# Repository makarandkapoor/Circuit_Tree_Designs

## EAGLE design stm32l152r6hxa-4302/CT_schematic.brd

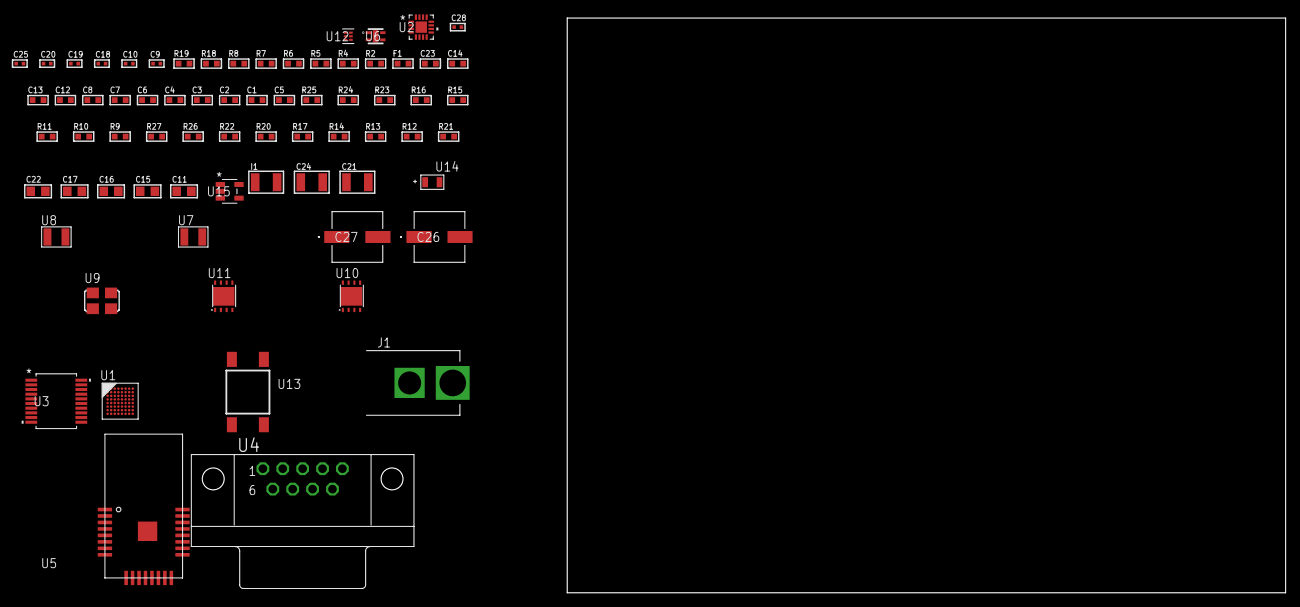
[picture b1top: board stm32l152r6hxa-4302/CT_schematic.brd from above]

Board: 2 copper layers, 100.0 x 80.0 mm, 71 parts (0 on the bottom side), 51 nets, no tracks yet.

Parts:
C1, C2, C3, C4, C6: 1e-07; C0603
C5: 4.7e-06; C0603
C7: 1e-08; C0603
C8, C12, C13, C14: 1e-06; C0603
C9, C10: 1e-11; C0402
C11, C15: 4.7e-06; C0805
C16, C17, C22: 1e-05; C0805
C18, C25: 1e-07; C0402
C19, C20, C28: 1e-08; C0402
C21, C24: 1e-05; C1210
C23: 8e-07; R0603
C26, C27: 0.0001; EXV-9H
F1: 240.0; L0603
I1: 1.5e-05; L1210
J1: PJ-037B; PJ-037B_PACKAGE
R2, R19: 1000.0; R0603
R4: 4700.0; R0603
R5, R6, R7, R8: 2200.0; R0603
R9, R10, R11, R15, R16, R23, R24: 10000.0; R0603
R12, R13, R14, R17, R20, R22: 100000.0; R0603
R18: 806.0; R0603
R21: 153694.38; R0603
R25: 82000.0; R0603
R26: 300000.0; R0603
R27: 120000.0; R0603
U1: STM32L152R6H6A; TFBGA64
U2: M41T65Q6F; M41T65_QFN-16
U3: MAX3218EAP+T; SSOP-20
U4: 182-009-113R531; 182-009-MALE
U5: ATBTLC1000-MR110CA
U6: Si7034-A10-IM; SI7034-A10-IM
U7, U8: ABS07-32.768KHZ-7-T
U9: ASFL1-25MHZ-NCS; ASFL1
U10: LP3878SDX-ADJ/NOPB; WSON-8
U11: LP2951ACSDX/NOPB; WSON-8
U12: TPS3895ADRYR; SON-6
U13: 4-1437565-2; SW_4-1437565-2
U14: Q65110A2395; LGM67K-G1J2-24-Z
U15: nc7sz125m5x; NC7SZ125M5X

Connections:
CLK_CRYSTAL_U1_A1: C9.1, U1.A1, U8.1
CLK_CRYSTAL_U1_B1: C10.1, U1.B1, U8.2
CLK_CRYSTAL_U2_1: U2.1, U7.1
CLK_CRYSTAL_U2_2: U2.2, U7.2
CLK_U1_C1: U1.C1, U9.3
GND: C1.2, C2.2, C3.2, C4.2, C5.2, C6.2, C7.2, C8.2, C9.2, C10.2, C11.2, C12.2, C13.2, C14.2, C16.2, C17.2, C18.2, C19.2, C20.2, C21.2, C22.2, C23.2, C24.2, C25.2, C26.2, C27.2, C28.2, J1.2, R2.2, R9.2, R19.2, R22.2, R25.2, R27.2, U1.C2, U1.D4, U1.D5, U1.D6, U1.F1, U2.3, U2.5, U2.17, U3.5, U3.17, U3.20, U4.5, U5.1, U5.9, U5.13, U5.24, U5.25, U6.5, U9.2, U10.3, U10.PAD, U11.3, U11.4, U11.PAD, U12.2, U14.C, U15.1, U15.3
NET_U1_A3: R6.1, U1.A3, U6.4
NET_U1_B2: C6.1, U1.B2
NET_U1_B3: R5.1, U1.B3, U6.2
NET_U1_B4: R9.1, U1.B4
NET_U1_E1: R4.1, U1.E1, U15.4
NET_U1_G7: R7.1, U1.G7, U2.10
NET_U1_H1: C7.1, C8.1, F1.1, U1.G1, U1.H1
NET_U1_H7: R8.1, U1.H7, U2.9
NET_U1_H8: U13.3, U13.4
NET_U2_4: R10.1, U2.4
NET_U2_11: R11.1, U2.11
NET_U3_1: I1.1, U3.1
NET_U3_2: R12.1, U3.2
NET_U3_3: R13.1, U3.3
NET_U3_4: R14.1, U3.4
NET_U3_15: C14.1, U3.15
NET_U3_16: C15.2, U3.16
NET_U3_18: C15.1, U3.18
NET_U3_19: C13.1, U3.19
NET_U4_2: U3.12, U4.2
NET_U4_3: U3.14, U4.3
NET_U4_7: U3.11, U4.7
NET_U4_8: U3.13, U4.8
NET_U5_17: R15.1, U5.17
NET_U5_20: R16.1, U5.20
NET_U10_1: C20.1, U10.1
NET_U10_6: R18.2, R19.1, U10.6
NET_U10_8: R17.1, U10.8
NET_U11_5: R20.1, U11.5
NET_U11_7: R21.2, R22.1, U11.7
NET_U12_1: R24.1, R25.1, U12.1
NET_U12_3: R26.2, R27.1, U12.3
NET_U12_4: R23.1, U12.4, U15.2
NET_U13_1: R2.1, U13.1, U13.2
PROC_SPI1_MISO: U1.A4, U5.14
PROC_SPI1_MOSI: U1.C4, U5.11
PROC_SPI1_NSS: U1.A6, U5.12
PROC_SPI1_SCK: U1.A5, U5.10
PROC_USART1_CTS: U1.C8, U3.8
PROC_USART1_RTS: U1.B8, U3.10
PROC_USART1_RX: U1.C3, U3.9
PROC_USART1_TX: U1.C7, U3.7
VCC_S1_15V4: C21.1, C23.1, C26.1, C27.1, J1.1, R17.2, U10.4, U11.8
VCC_TIER1_1V8: C1.1, C2.1, C3.1, C4.1, C5.1, C11.1, C12.1, C16.1, C17.1, C18.1, C22.1, C25.1, C28.1, F1.2, I1.2, R4.2, R5.2, R6.2, R7.2, R8.2, R10.2, R11.2, R12.2, R13.2, R14.2, R15.2, R16.2, R18.1, R23.2, R24.2, R26.1, U1.D2, U1.E4, U1.E5, U1.E6, U2.14, U3.6, U5.6, U5.22, U6.1, U10.5, U12.6, U15.5
VCC_TIER1_3V3: C19.1, C24.1, R20.2, R21.1, U9.4, U11.1

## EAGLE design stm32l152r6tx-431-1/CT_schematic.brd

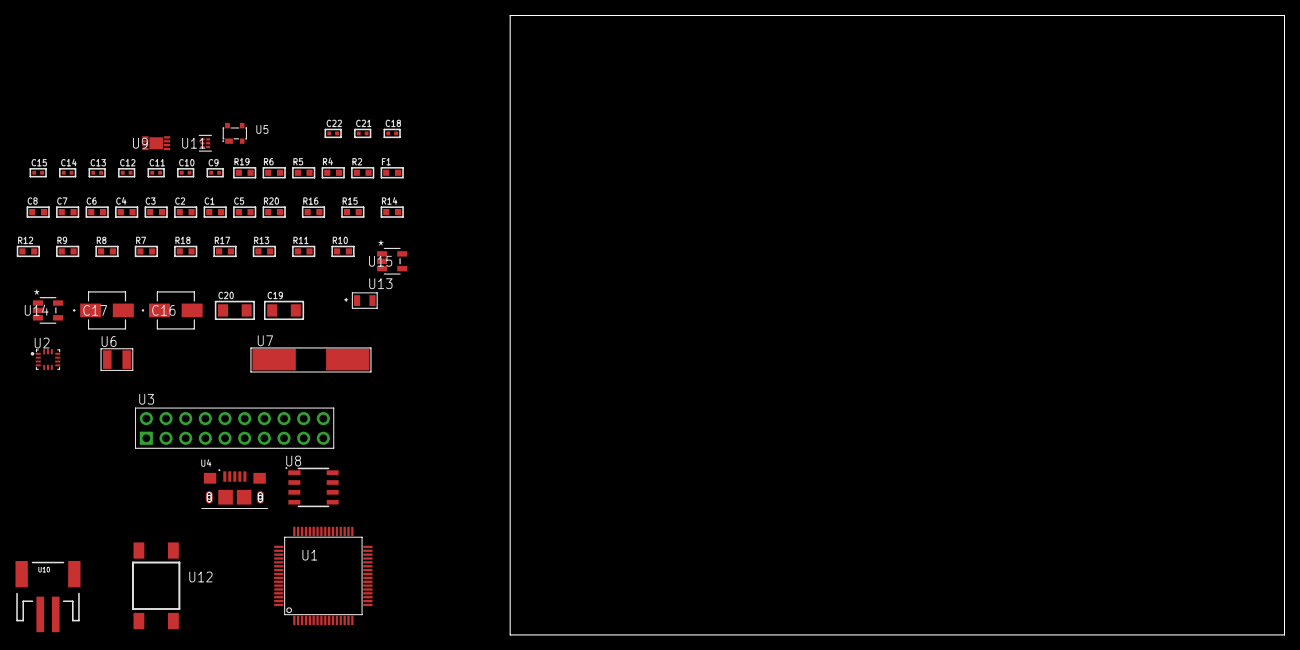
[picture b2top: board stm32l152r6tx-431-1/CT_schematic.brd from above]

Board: 2 copper layers, 56 parts (0 on the bottom side), 32 nets, no tracks yet.

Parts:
C1, C2, C3, C4, C6: 1e-07; C0603
C5: 4.7e-06; C0603
C7: 1e-08; C0603
C8: 1e-06; C0603
C9, C10, C11, C12: 1e-11; C0402
C13, C14, C15, C18: 1e-07; C0402
C16: 1e-06; EXV-9B
C17: 2.2e-06; EXV-9B
C19, C20: 1e-05; C1206
C21, C22: 1e-08; C0402
F1: 240.0; L0603
R2: 1000.0; R0603
R4: 4700.0; R0603
R5, R6: 2200.0; R0603
R7, R8, R9, R14, R15, R20: 10000.0; R0603
R10, R11, R13: 100000.0; R0603
R12: 47000.0; R0603
R16: 82000.0; R0603
R17: 300000.0; R0603
R18: 120000.0; R0603
R19: 2000.0; R0603
U1: STM32L152R6T6; LQFP64
U2: BMG250; LGA-14
U3: TST-110-05-T-D-RA
U4: 10118193-0001LF; FCI_10118193-0001LF
U5: prtr5v0u2ax; SOT143B
U6: ABS07-32.768KHZ-7-T
U7: ABLS-25.000MHZ-B2F-T
U8: LP2954AIMX/NOPB; LP2954
U9: MCP73831T-2ACI/MC; DFN8_2X3MC
U10: S2B-PH-SM4-TB(LF)(SN); JST-2-SMD
U11: TPS3895ADRYR; SON-6
U12: 4-1437565-2; SW_4-1437565-2
U13: Q65110A2395; LGM67K-G1J2-24-Z
U14, U15: nc7sz125m5x; NC7SZ125M5X

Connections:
CLK_CRYSTAL_U1_3: C9.1, U1.3, U6.1
CLK_CRYSTAL_U1_4: C10.1, U1.4, U6.2
CLK_CRYSTAL_U1_5: C11.1, U1.5, U7.1
CLK_CRYSTAL_U1_6: C12.1, U1.6, U7.2
GND: C1.2, C2.2, C3.2, C4.2, C5.2, C6.2, C7.2, C8.2, C9.2, C10.2, C11.2, C12.2, C13.2, C14.2, C15.2, C16.2, C17.2, C18.2, C19.2, C20.2, C21.2, C22.2, R2.2, R7.2, R13.2, R16.2, R18.2, R19.2, U1.12, U1.18, U1.31, U1.47, U1.63, U2.1, U2.6, U2.7, U3.4, U3.6, U3.8, U3.10, U3.12, U3.14, U3.16, U3.18, U3.20, U4.5, U4.6, U4.7, U4.8, U4.9, U5.1, U8.4, U9.6, U9.9, U10.2, U11.2, U13.C, U14.2, U14.3, U15.1, U15.3
INPUT_USBPOWER_5V: C19.1, R20.2, U4.1, U5.4, U9.1, U9.2
NET_U1_1: C6.1, U1.1
NET_U1_7: R4.1, U1.7, U15.4
NET_U1_13: C7.1, C8.1, F1.1, U1.13
NET_U1_58: R5.1, U1.58, U2.13
NET_U1_59: R6.1, U1.59, U2.14
NET_U1_60: R7.1, U1.60
NET_U1_62: U12.3, U12.4
NET_U2_12: R8.1, U2.12
NET_U8_3: R11.1, U8.3
NET_U8_5: R10.1, U8.5
NET_U8_7: R12.2, R13.1, U8.7
NET_U9_5: R20.1, U9.5
NET_U9_8: R19.1, U9.8
NET_U11_1: R15.1, R16.1, U11.1
NET_U11_3: R17.2, R18.1, U11.3
NET_U11_4: R14.1, U11.4, U14.4, U15.2
NET_U12_1: R2.1, U12.1, U12.2
PROC_GPIO_TO_U2_INT1: U1.2, U2.4
PROC_SYS_JTCK_SWCLK: U1.49, U3.9
PROC_SYS_JTDO_TRACESWO: U1.55, U3.13
PROC_SYS_JTMS_SWDIO: U1.46, U3.7
PROC_USB_DM: U1.44, U4.2, U5.3
PROC_USB_DP: U1.45, U4.3, U5.2
RST_OUT_U3_SRESET_B: R9.1, U3.15, U14.1
VCC_S1_3V7: C16.1, C20.1, R11.2, U8.8, U9.3, U9.4, U10.1
VCC_TIER1_1V8: C1.1, C2.1, C3.1, C4.1, C5.1, C13.1, C14.1, C15.1, C17.1, C18.1, C21.1, C22.1, F1.2, R4.2, R5.2, R6.2, R8.2, R9.2, R10.2, R12.1, R14.2, R15.2, R17.1, U1.19, U1.32, U1.48, U1.64, U2.5, U2.8, U3.1, U8.1, U11.6, U14.5, U15.5

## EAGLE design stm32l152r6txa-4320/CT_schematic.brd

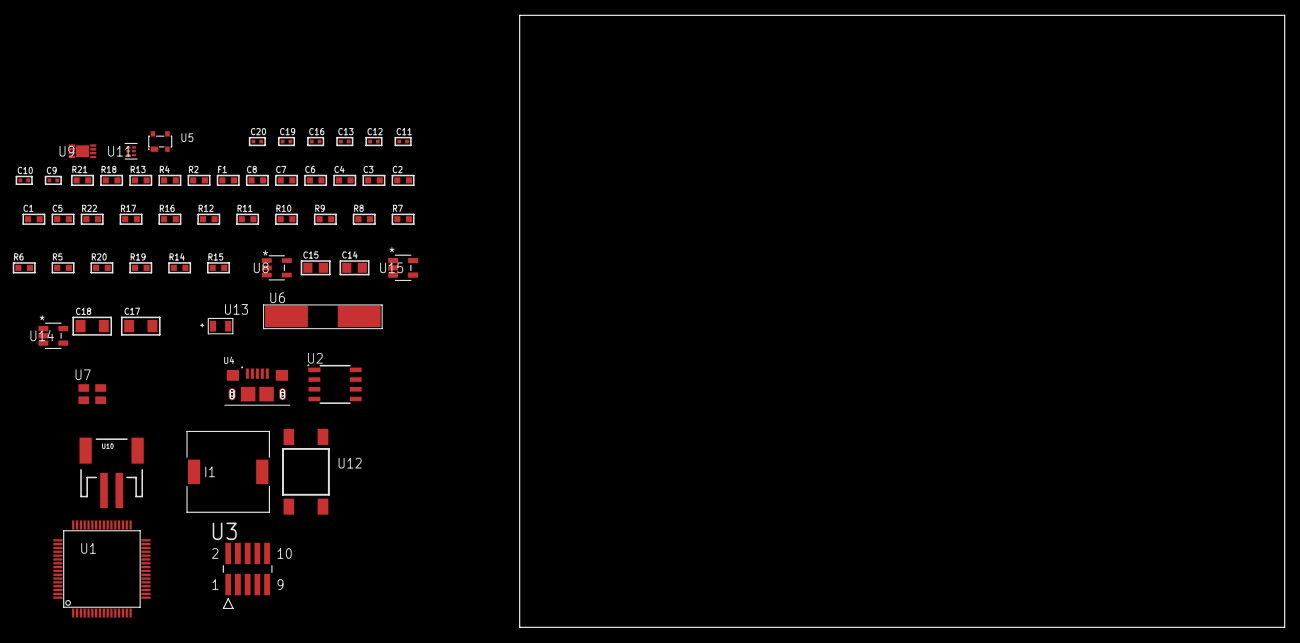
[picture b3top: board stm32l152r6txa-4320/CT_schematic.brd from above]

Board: 2 copper layers, 57 parts (0 on the bottom side), 35 nets, no tracks yet.

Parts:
C1, C2, C3, C4, C6: 1e-07; C0603
C5: 4.7e-06; C0603
C7: 1e-08; C0603
C8: 1e-06; C0603
C9, C10: 1e-11; C0402
C11, C13, C19, C20: 1e-08; C0402
C12, C16: 1e-07; C0402
C14, C15: 1e-05; C0805
C17, C18: 1e-05; C1206
F1: 240.0; L0603
I1: 3.8e-06; DR1040
R2: 1000.0; R0603
R4: 4700.0; R0603
R5, R6, R7, R8, R9, R10, R11, R12, R16, R17, R22: 10000.0; R0603
R13: 5.0; R0603
R14: 220000.0; R0603
R15: 1000000.0; R0603
R18: 9100.0; R0603
R19: 680000.0; R0603
R20: 120000.0; R0603
R21: 2000.0; R0603
U1: STM32L152R6T6A; LQFP64
U2: AT25256B-SSHL-T; SOIC-8
U3: FTSH-105-01-L-DV-K; SAMTEC_FTSH-105-01-L-DV-K
U4: 10118193-0001LF; FCI_10118193-0001LF
U5: prtr5v0u2ax; SOT143B
U6: ABLS-25.000MHZ-B2F-T
U7: ASEK-32.768KHz-ECST; ASEK
U8: ltc3406es5; TSOT-23-5
U9: MCP73831T-2ACI/MC; DFN8_2X3MC
U10: S2B-PH-SM4-TB(LF)(SN); JST-2-SMD
U11: TPS3895ADRYR; SON-6
U12: 4-1437565-2; SW_4-1437565-2
U13: Q65110A2395; LGM67K-G1J2-24-Z
U14, U15: nc7sz125m5x; NC7SZ125M5X

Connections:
CLK_CRYSTAL_U1_5: C9.1, U1.5, U6.1
CLK_CRYSTAL_U1_6: C10.1, U1.6, U6.2
CLK_U1_3: U1.3, U7.3
GND: C1.2, C2.2, C3.2, C4.2, C5.2, C6.2, C7.2, C8.2, C9.2, C10.2, C11.2, C12.2, C13.2, C14.2, C15.1, C15.2, C16.2, C17.2, C18.2, C19.2, C20.2, R2.2, R5.2, R12.2, R13.2, R14.2, R18.2, R20.2, R21.2, U1.12, U1.18, U1.31, U1.47, U1.63, U2.4, U3.3, U3.5, U4.5, U4.6, U4.7, U4.8, U4.9, U5.1, U7.2, U8.2, U9.6, U9.9, U10.2, U11.2, U13.C, U14.2, U14.3, U15.1, U15.3
INPUT_USBPOWER_5V: C17.1, R22.2, U4.1, U5.4, U9.1, U9.2
NET_U1_1: C6.1, U1.1
NET_U1_7: R4.1, U1.7, U15.4
NET_U1_13: C7.1, C8.1, F1.1, U1.13
NET_U1_60: R5.1, U1.60
NET_U1_62: U12.3, U12.4
NET_U2_3: R6.1, U2.3
NET_U2_7: R8.1, U2.7
NET_U3_9: R13.1, U3.9
NET_U8_3: I1.1, U8.3
NET_U8_5: R14.1, R15.1, U8.5
NET_U8_ATNET_3: I1.2, R15.2
NET_U9_5: R22.1, U9.5
NET_U9_8: R21.1, U9.8
NET_U11_1: R17.1, R18.1, U11.1
NET_U11_3: R19.2, R20.1, U11.3
NET_U11_4: R16.1, U11.4, U14.4, U15.2
NET_U12_1: R2.1, U12.1, U12.2
PROC_SPI1_MISO: U1.22, U2.2
PROC_SPI1_MOSI: U1.23, U2.5
PROC_SPI1_NSS: R7.1, U1.20, U2.1
PROC_SPI1_SCK: U1.21, U2.6
PROC_SYS_JTCK_SWCLK: R12.1, U1.49, U3.4
PROC_SYS_JTDI: R10.1, U1.50, U3.8
PROC_SYS_JTDO_TRACESWO: U1.55, U3.6
PROC_SYS_JTMS_SWDIO: R11.1, U1.46, U3.2
PROC_USB_DM: U1.44, U4.2, U5.3
PROC_USB_DP: U1.45, U4.3, U5.2
RST_OUT_U3_JTAG_RST_B: R9.1, U3.10, U14.1
VCC_S1_3V7: C14.1, C18.1, U8.4, U9.3, U9.4, U10.1
VCC_TIER1_3V3: C1.1, C2.1, C3.1, C4.1, C5.1, C11.1, C12.1, C13.1, C15.2, C16.1, C19.1, C20.1, F1.2, I1.2, R4.2, R6.2, R7.2, R8.2, R9.2, R10.2, R11.2, R15.2, R16.2, R17.2, R19.1, U1.19, U1.32, U1.48, U1.64, U2.8, U3.1, U7.4, U11.6, U14.5, U15.5

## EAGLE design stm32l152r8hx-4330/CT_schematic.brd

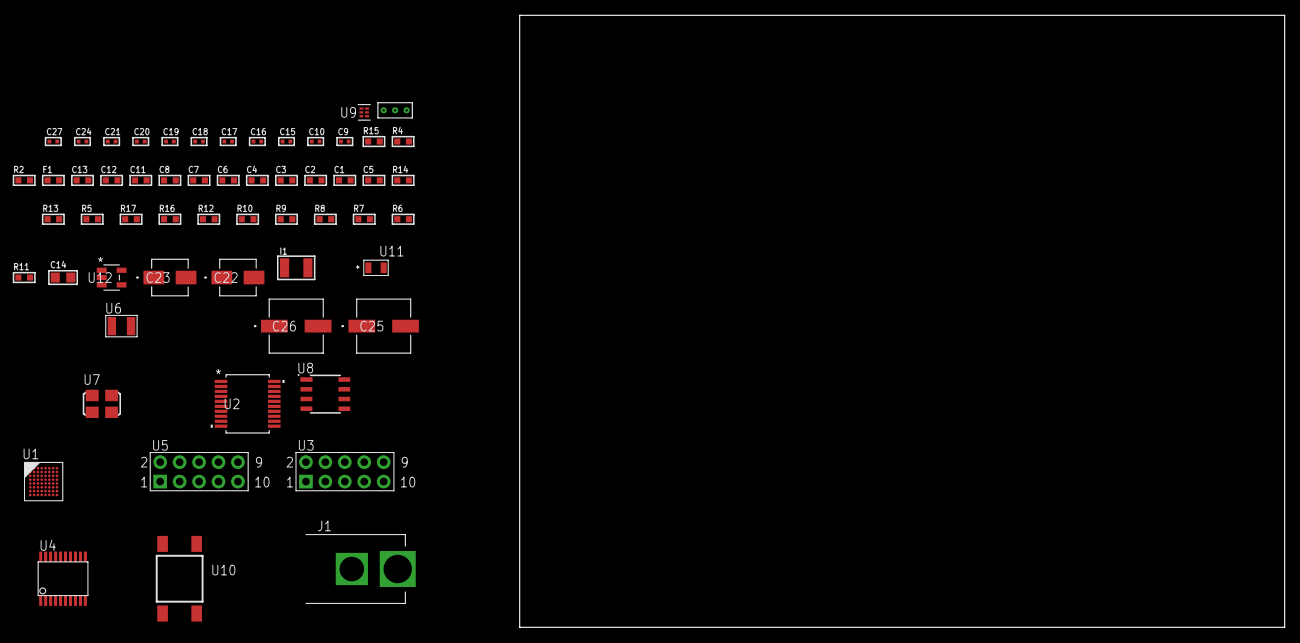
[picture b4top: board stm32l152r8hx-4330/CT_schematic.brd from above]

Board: 2 copper layers, 100.0 x 80.0 mm, 58 parts (0 on the bottom side), 50 nets, no tracks yet.

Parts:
C1, C2, C3, C4, C6: 1e-07; C0603
C5: 4.7e-06; C0603
C7: 1e-08; C0603
C8, C11, C12, C13: 1e-06; C0603
C9, C10: 1e-11; C0402
C14: 4.7e-06; C0805
C15, C16, C17, C18, C19, C20, C24: 1e-07; C0402
C21, C27: 1e-08; C0402
C22: 1e-06; EXV-9B
C23: 2.2e-06; EXV-9B
C25, C26: 0.0001; EXV-9H
F1: 240.0; L0603
I1: 1.5e-05; L1210
J1: PJ-037B; PJ-037B_PACKAGE
R2: 1000.0; R0603
R4: 4700.0; R0603
R5, R13, R14: 10000.0; R0603
R6, R7, R8, R9, R10, R12: 100000.0; R0603
R11: 164658.62; R0603
R15: 9100.0; R0603
R16: 680000.0; R0603
R17: 120000.0; R0603
U1: STM32L152R8H6; TFBGA64
U2: MAX3218EAP+T; SSOP-20
U3, U5: HTSS-105-01-G-D
U4: SP3203ECY-L/TR; TSSOP20-I
U6: ABS07-32.768KHZ-7-T
U7: ASFL1-25MHZ-NCS; ASFL1
U8: LP2954AIMX/NOPB; LP2954
U9: TPS3895ADRYR; SON-6
U10: 4-1437565-2; SW_4-1437565-2
U11: Q65110A2395; LGM67K-G1J2-24-Z
U12: nc7sz125m5x; NC7SZ125M5X
U13: Dummy; DUMMY_PACKAGE_119

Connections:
CLK_CRYSTAL_U1_A1: C9.1, U1.A1, U6.1
CLK_CRYSTAL_U1_B1: C10.1, U1.B1, U6.2
CLK_U1_C1: U1.C1, U7.3
GND: C1.2, C2.2, C3.2, C4.2, C5.2, C6.2, C7.2, C8.2, C9.2, C10.2, C11.2, C12.2, C13.2, C15.2, C16.2, C19.2, C20.2, C21.2, C22.2, C23.2, C24.2, C25.2, C26.2, C27.2, J1.2, R2.2, R5.2, R12.2, R15.2, R17.2, U1.C2, U1.D4, U1.D5, U1.D6, U1.F1, U2.5, U2.17, U2.20, U3.9, U4.18, U5.9, U7.2, U8.4, U9.2, U11.C, U12.1, U12.3, U13.1
NET_U1_B2: C6.1, U1.B2
NET_U1_B4: R5.1, U1.B4
NET_U1_E1: R4.1, U1.E1, U12.4
NET_U1_H1: C7.1, C8.1, F1.1, U1.G1, U1.H1
NET_U1_H8: U10.3, U10.4
NET_U2_1: I1.1, U2.1
NET_U2_2: R6.1, U2.2
NET_U2_3: R7.1, U2.3
NET_U2_4: R8.1, U2.4
NET_U2_15: C13.1, U2.15
NET_U2_16: C14.2, U2.16
NET_U2_18: C14.1, U2.18
NET_U2_19: C12.1, U2.19
NET_U3_3: U2.12, U3.3
NET_U3_4: U2.11, U3.4
NET_U3_5: U2.14, U3.5
NET_U3_6: U2.13, U3.6
NET_U4_1: C17.1, U4.1
NET_U4_2: C19.1, U4.2
NET_U4_3: C17.2, U4.3
NET_U4_4: C18.1, U4.4
NET_U4_5: C18.2, U4.5
NET_U4_6: C20.1, U4.6
NET_U5_3: U4.14, U5.3
NET_U5_4: U4.13, U5.4
NET_U5_5: U4.17, U5.5
NET_U5_6: U4.16, U5.6
NET_U8_3: R10.1, U8.3
NET_U8_5: R9.1, U8.5
NET_U8_7: R11.2, R12.1, U8.7
NET_U9_1: R14.1, R15.1, U9.1
NET_U9_3: R16.2, R17.1, U9.3
NET_U9_4: R13.1, U9.4, U12.2
NET_U10_1: R2.1, U10.1, U10.2
PROC_PB9: U1.A3, U13.3
PROC_PC13_WKUP2: U1.A2, U13.2
PROC_USART1_CTS: U1.C8, U2.8
PROC_USART1_RTS: U1.B8, U2.10
PROC_USART1_RX: U1.C3, U2.9
PROC_USART1_TX: U1.C7, U2.7
PROC_USART2_CTS: U1.G2, U4.8
PROC_USART2_RTS: U1.H2, U4.10
PROC_USART2_RX: U1.G3, U4.11
PROC_USART2_TX: U1.F3, U4.7
VCC_S1_6V7: C22.1, C25.1, C26.1, J1.1, R10.2, U8.8
VCC_TIER1_3V3: C1.1, C2.1, C3.1, C4.1, C5.1, C11.1, C15.1, C16.1, C21.1, C23.1, C24.1, C27.1, F1.2, I1.2, R4.2, R6.2, R7.2, R8.2, R9.2, R11.1, R13.2, R14.2, R16.1, U1.D2, U1.E4, U1.E5, U1.E6, U2.6, U4.12, U4.19, U7.4, U8.1, U9.6, U12.5

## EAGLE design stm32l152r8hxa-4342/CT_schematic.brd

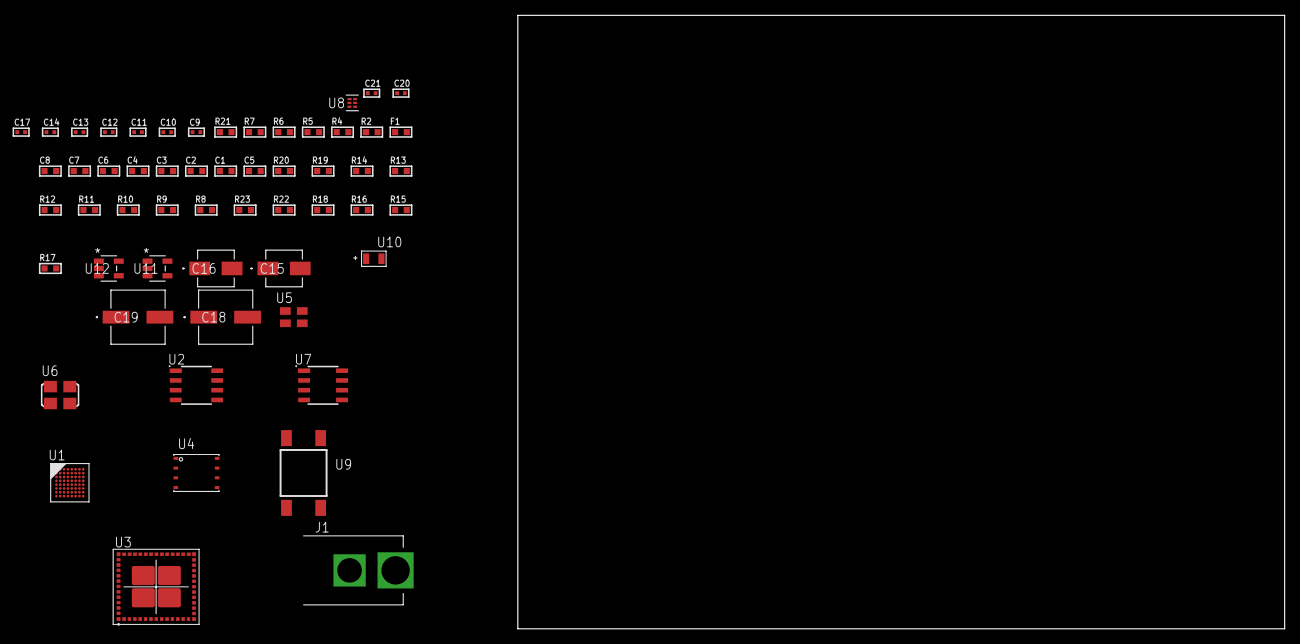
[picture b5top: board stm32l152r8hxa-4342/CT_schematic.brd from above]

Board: 2 copper layers, 100.0 x 80.0 mm, 56 parts (0 on the bottom side), 33 nets, no tracks yet.

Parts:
C1, C2, C3, C4, C6: 1e-07; C0603
C5: 4.7e-06; C0603
C7: 1e-08; C0603
C8: 1e-06; C0603
C9, C12, C13, C14, C20, C21: 1e-08; C0402
C10, C11, C17: 1e-07; C0402
C15: 1e-06; EXV-9B
C16: 2.2e-06; EXV-9B
C18, C19: 0.0001; EXV-9H
F1: 240.0; L0603
J1: PJ-037B; PJ-037B_PACKAGE
R2: 1000.0; R0603
R4, R5: 4700.0; R0603
R6, R7: 2200.0; R0603
R8, R9, R10, R11, R12, R13, R14, R19, R20: 10000.0; R0603
R15, R16, R18: 100000.0; R0603
R17: 164658.62; R0603
R21: 9100.0; R0603
R22: 680000.0; R0603
R23: 120000.0; R0603
U1: STM32L152R8H6A; TFBGA64
U2: AT25160B-SSHL-T; SOIC-8
U3: MBH7BLZ02-109004
U4: 24AA256-I/MF; DFN8-S
U5: ASEK-32.768KHz-ECST; ASEK
U6: ASFL1-25MHZ-NCS; ASFL1
U7: LP2954AIMX/NOPB; LP2954
U8: TPS3895ADRYR; SON-6
U9: 4-1437565-2; SW_4-1437565-2
U10: Q65110A2395; LGM67K-G1J2-24-Z
U11, U12: nc7sz125m5x; NC7SZ125M5X

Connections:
CLK_U1_A1: U1.A1, U5.3
CLK_U1_C1: U1.C1, U6.3
GND: C1.2, C2.2, C3.2, C4.2, C5.2, C6.2, C7.2, C8.2, C9.2, C10.2, C11.2, C12.2, C13.2, C14.2, C15.2, C16.2, C17.2, C18.2, C19.2, C20.2, C21.2, J1.2, R2.2, R8.2, R13.2, R18.2, R21.2, R23.2, U1.C2, U1.D4, U1.D5, U1.D6, U1.F1, U2.4, U3.1, U3.3, U3.15, U3.27, U3.29, U3.41, U3.42, U3.43, U3.44, U3.45, U3.46, U3.47, U3.48, U3.49, U3.50, U3.52, U3.53, U3.54, U3.55, U3.56, U4.4, U5.2, U6.2, U7.4, U8.2, U10.C, U11.1, U11.3, U12.1, U12.3
NET_U1_A3: R7.1, U1.A3, U4.5
NET_U1_B2: C6.1, U1.B2
NET_U1_B3: R6.1, U1.B3, U4.6
NET_U1_B4: R8.1, U1.B4
NET_U1_E1: R5.1, U1.E1, U12.4
NET_U1_H1: C7.1, C8.1, F1.1, U1.G1, U1.H1
NET_U1_H8: U9.3, U9.4
NET_U2_3: R9.1, U2.3
NET_U2_7: R11.1, U2.7
NET_U3_39: R4.1, U3.39, U11.4
NET_U4_1: R12.1, U4.1
NET_U4_2: R13.1, U4.2
NET_U4_3: R14.1, U4.3
NET_U7_3: R16.1, U7.3
NET_U7_5: R15.1, U7.5
NET_U7_7: R17.2, R18.1, U7.7
NET_U8_1: R20.1, R21.1, U8.1
NET_U8_3: R22.2, R23.1, U8.3
NET_U8_4: R19.1, U8.4, U11.2, U12.2
NET_U9_1: R2.1, U9.1, U9.2
PROC_SPI1_MISO: U1.A4, U2.2
PROC_SPI1_MOSI: U1.C4, U2.5
PROC_SPI1_NSS: R10.1, U1.A6, U2.1
PROC_SPI1_SCK: U1.A5, U2.6
PROC_USART1_CTS: U1.C8, U3.26
PROC_USART1_RTS: U1.B8, U3.24
PROC_USART1_RX: U1.C3, U3.25
PROC_USART1_TX: U1.C7, U3.23
VCC_S1_6V0: C15.1, C18.1, C19.1, J1.1, R16.2, U7.8
VCC_TIER1_3V3: C1.1, C2.1, C3.1, C4.1, C5.1, C9.1, C10.1, C11.1, C12.1, C13.1, C14.1, C16.1, C17.1, C20.1, C21.1, F1.2, R4.2, R5.2, R6.2, R7.2, R9.2, R10.2, R11.2, R12.2, R14.2, R15.2, R17.1, R19.2, R20.2, R22.1, U1.D2, U1.E4, U1.E5, U1.E6, U2.8, U3.28, U4.7, U4.8, U5.4, U6.4, U7.1, U8.6, U11.5, U12.5

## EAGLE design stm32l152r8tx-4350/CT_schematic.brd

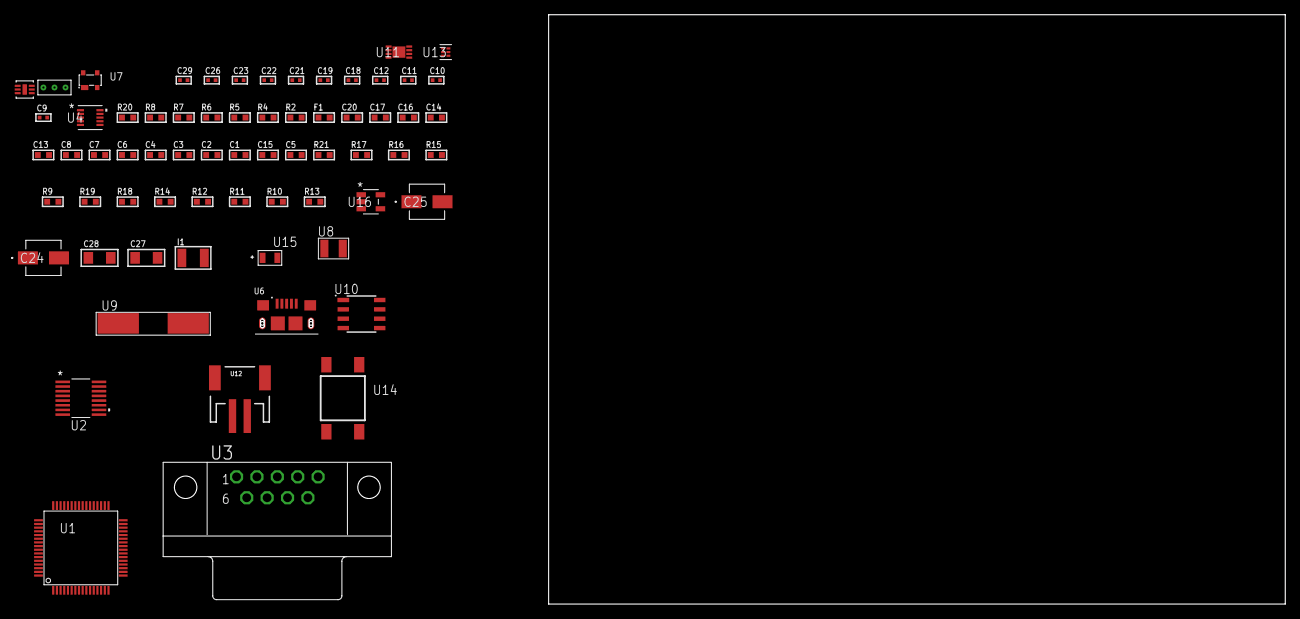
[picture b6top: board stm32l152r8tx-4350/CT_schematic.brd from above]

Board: 2 copper layers, 67 parts (0 on the bottom side), 45 nets, no tracks yet.

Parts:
C1, C2, C3, C4, C6: 1e-07; C0603
C5: 4.7e-06; C0603
C7: 1e-08; C0603
C8, C13, C14, C16, C17, C20: 1e-06; C0603
C9, C10, C11, C12: 1e-11; C0402
C15: 2.2e-07; C0603
C18, C19, C21, C22, C23, C26: 1e-07; C0402
C24: 1e-06; EXV-9B
C25: 2.2e-06; EXV-9B
C27, C28: 1e-05; C1206
C29: 1e-08; C0402
F1: 240.0; L0603
I1: 1e-05; L1210
R2: 1000.0; R0603
R4: 4700.0; R0603
R5, R6, R7, R8: 2200.0; R0603
R9, R15, R16, R21: 10000.0; R0603
R10, R11, R12, R14: 100000.0; R0603
R13: 101022.32; R0603
R17: 18000.0; R0603
R18: 470000.0; R0603
R19: 120000.0; R0603
R20: 2000.0; R0603
U1: STM32L152R8T6; LQFP64
U2: LTC2804CGN-1#PBF; SSOP-16
U3: 182-009-113R531; 182-009-MALE
U4: MAG3110FCR1; DFN-10
U5: SI7006-A20-IM; DFN-6
U6: 10118193-0001LF; FCI_10118193-0001LF
U7: prtr5v0u2ax; SOT143B
U8: ABS07-32.768KHZ-7-T
U9: ABLS-25.000MHZ-B2F-T
U10: LP2954AIMX/NOPB; LP2954
U11: MCP73831T-2ACI/MC; DFN8_2X3MC
U12: S2B-PH-SM4-TB(LF)(SN); JST-2-SMD
U13: TPS3895ADRYR; SON-6
U14: 4-1437565-2; SW_4-1437565-2
U15: Q65110A2395; LGM67K-G1J2-24-Z
U16: nc7sz125m5x; NC7SZ125M5X
U17: Dummy; DUMMY_PACKAGE_144

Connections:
CLK_CRYSTAL_U1_3: C9.1, U1.3, U8.1
CLK_CRYSTAL_U1_4: C10.1, U1.4, U8.2
CLK_CRYSTAL_U1_5: C11.1, U1.5, U9.1
CLK_CRYSTAL_U1_6: C12.1, U1.6, U9.2
GND: C1.2, C2.2, C3.2, C4.2, C5.2, C6.2, C7.2, C8.2, C9.2, C10.2, C11.2, C12.2, C13.2, C14.2, C16.2, C17.2, C18.2, C19.2, C20.2, C21.2, C22.2, C23.2, C24.2, C25.2, C26.2, C27.2, C28.2, C29.2, R2.2, R9.2, R14.2, R17.2, R19.2, R20.2, U1.12, U1.18, U1.31, U1.47, U1.63, U2.8, U3.5, U4.5, U4.10, U5.2, U5.7, U6.5, U6.6, U6.7, U6.8, U6.9, U7.1, U10.4, U11.6, U11.9, U12.2, U13.2, U15.C, U16.1, U16.3, U17.1
INPUT_USBPOWER_5V: C27.1, R21.2, U6.1, U7.4, U11.1, U11.2
NET_U1_1: C6.1, U1.1
NET_U1_7: R4.1, U1.7, U16.4
NET_U1_13: C7.1, C8.1, F1.1, U1.13
NET_U1_29: R7.1, U1.29, U5.6
NET_U1_30: R8.1, U1.30, U5.1
NET_U1_58: R5.1, U1.58, U4.7
NET_U1_59: R6.1, U1.59, U4.6
NET_U1_60: R9.1, U1.60
NET_U1_62: U14.3, U14.4
NET_U2_6: C13.1, U2.6
NET_U2_7: C15.1, I1.2, U2.7
NET_U2_9: C14.1, U2.9
NET_U2_10: C15.2, U2.10
NET_U2_11: R10.1, U2.11
NET_U3_2: U2.1, U3.2
NET_U3_3: U2.3, U3.3
NET_U3_7: U2.2, U3.7
NET_U3_8: U2.4, U3.8
NET_U4_1: C18.1, U4.1
NET_U4_4: C21.1, U4.4
NET_U10_3: R12.1, U10.3
NET_U10_5: R11.1, U10.5
NET_U10_7: R13.2, R14.1, U10.7
NET_U11_5: R21.1, U11.5
NET_U11_8: R20.1, U11.8
NET_U13_1: R16.1, R17.1, U13.1
NET_U13_3: R18.2, R19.1, U13.3
NET_U13_4: R15.1, U13.4, U16.2
NET_U14_1: R2.1, U14.1, U14.2
PROC_ADC_IN13: U1.11, U17.3
PROC_ADC_IN20: U1.35, U17.2
PROC_USART2_CTS: U1.14, U2.13
PROC_USART2_RTS: U1.15, U2.15
PROC_USART2_RX: U1.17, U2.16
PROC_USART2_TX: U1.16, U2.14
PROC_USB_DM: U6.2, U7.3
PROC_USB_DP: U6.3, U7.2
VCC_S1_3V7: C24.1, C28.1, R12.2, U10.8, U11.3, U11.4, U12.1
VCC_TIER1_2V5: C1.1, C2.1, C3.1, C4.1, C5.1, C16.1, C17.1, C19.1, C20.1, C22.1, C23.1, C25.1, C26.1, C29.1, F1.2, I1.1, R4.2, R5.2, R6.2, R7.2, R8.2, R10.2, R11.2, R13.1, R15.2, R16.2, R18.1, U1.19, U1.32, U1.48, U1.64, U2.5, U2.12, U4.2, U4.8, U5.5, U10.1, U13.6, U16.5

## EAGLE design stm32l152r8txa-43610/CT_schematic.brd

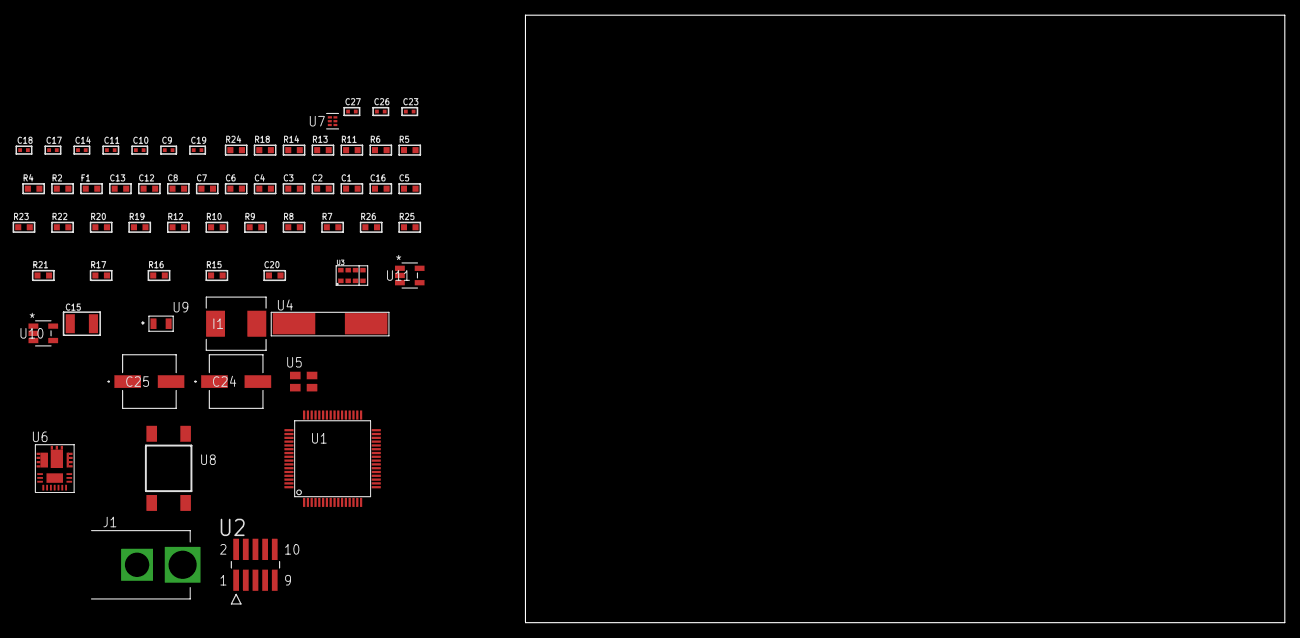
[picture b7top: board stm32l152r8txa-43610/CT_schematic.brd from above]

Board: 2 copper layers, 100.0 x 80.0 mm, 63 parts (0 on the bottom side), 34 nets, no tracks yet.

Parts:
C1, C2, C3, C4, C6: 1e-07; C0603
C5: 4.7e-06; C0603
C7: 1e-08; C0603
C8, C12, C13: 1e-06; C0603
C9, C10: 1e-11; C0402
C11, C17, C18, C23: 1e-07; C0402
C14, C26, C27: 1e-08; C0402
C15: 0.0001; C1210
C16: 2.2e-06; C0603
C19: 8.2e-09; C0402
C20: 2.7074646757046e-07; R0603
C24, C25: 0.0001; EXV-9H
F1: 240.0; L0603
I1: 6.8e-07; IND25X25CZ
J1: PJ-037B; PJ-037B_PACKAGE
R2: 1000.0; R0603
R4: 4700.0; R0603
R5, R6: 2200.0; R0603
R7, R8, R9, R10, R12, R22, R23: 10000.0; R0603
R11: 5.0; R0603
R13: 22.0; R0603
R14: 0.1; R0603
R15: 4030.2416170974; R0603
R16: 719.68600305311; R0603
R17: 64.186993865031; R0603
R18: 130.0; R0603
R19: 39000.0; R0603
R20: 49900.0; R0603
R21: 5322.6666666667; R0603
R24: 9100.0; R0603
R25: 680000.0; R0603
R26: 120000.0; R0603
U1: STM32L152R8T6A; LQFP64
U2: FTSH-105-01-L-DV-K; SAMTEC_FTSH-105-01-L-DV-K
U3: TMD27711; SMD-8
U4: ABLS-25.000MHZ-B2F-T
U5: ASEK-32.768KHz-ECST; ASEK
U6: IR3899MTR1PBF
U7: TPS3895ADRYR; SON-6
U8: 4-1437565-2; SW_4-1437565-2
U9: Q65110A2395; LGM67K-G1J2-24-Z
U10, U11: nc7sz125m5x; NC7SZ125M5X

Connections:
CLK_CRYSTAL_U1_5: C9.1, U1.5, U4.1
CLK_CRYSTAL_U1_6: C10.1, U1.6, U4.2
CLK_U1_3: U1.3, U5.3
GND: C1.2, C2.2, C3.2, C4.2, C5.2, C6.2, C7.2, C8.2, C9.2, C10.2, C11.2, C12.2, C13.2, C14.2, C16.2, C17.2, C18.2, C23.2, C24.2, C25.2, C26.2, C27.2, J1.2, R2.2, R7.2, R11.2, R14.1, R14.2, R16.2, R19.2, R21.2, R24.2, R26.2, U1.12, U1.18, U1.31, U1.47, U1.63, U2.3, U2.5, U3.3, U5.2, U6.4, U6.11, U6.17, U7.2, U9.C, U10.2, U10.3, U11.1, U11.3
NET_U1_1: C6.1, U1.1
NET_U1_7: R4.1, U1.7, U11.4
NET_U1_13: C7.1, C8.1, F1.1, U1.13
NET_U1_58: R5.1, U1.58, U3.2
NET_U1_59: R6.1, U1.59, U3.8
NET_U1_60: R7.1, U1.60
NET_U1_62: U8.3, U8.4
NET_U2_9: R11.1, U2.9
NET_U3_4: C13.1, R13.1, U3.4
NET_U3_7: R12.1, U3.7
NET_U6_1: C19.1, R15.1, R16.1, R17.1, R18.1, U6.1, U6.8
NET_U6_2: C18.1, U6.2
NET_U6_3: C19.2, C20.1, C20.2, U6.3
NET_U6_5: R19.1, U6.5
NET_U6_10: C16.1, U6.10
NET_U6_12: C15.1, I1.1, U6.12
NET_U6_14: C15.2, U6.14
NET_U6_15: R20.1, R21.1, U6.15
NET_U6_ATNET_3: I1.2, R15.2
NET_U6_ATNET_4: C20.2, R17.2
NET_U7_1: R23.1, R24.1, U7.1
NET_U7_3: R25.2, R26.1, U7.3
NET_U7_4: R22.1, U7.4, U10.4, U11.2
NET_U8_1: R2.1, U8.1, U8.2
PROC_SYS_JTCK_SWCLK: R9.1, U1.49, U2.4
PROC_SYS_JTDO_TRACESWO: U1.55, U2.6
PROC_SYS_JTMS_SWDIO: R10.1, U1.46, U2.2
RST_OUT_U2_JTAG_RST_B: R8.1, U2.10, U10.1
VCC_S1_16V3: C17.1, C24.1, C25.1, J1.1, R20.2, U6.9
VCC_TIER1_3V3: C1.1, C2.1, C3.1, C4.1, C5.1, C11.1, C12.1, C14.1, C23.1, C26.1, C27.1, F1.2, I1.2, R4.2, R5.2, R6.2, R8.2, R9.2, R10.2, R12.2, R13.2, R15.2, R22.2, R23.2, R25.1, U1.19, U1.32, U1.48, U1.64, U2.1, U3.1, U5.4, U7.6, U10.5, U11.5

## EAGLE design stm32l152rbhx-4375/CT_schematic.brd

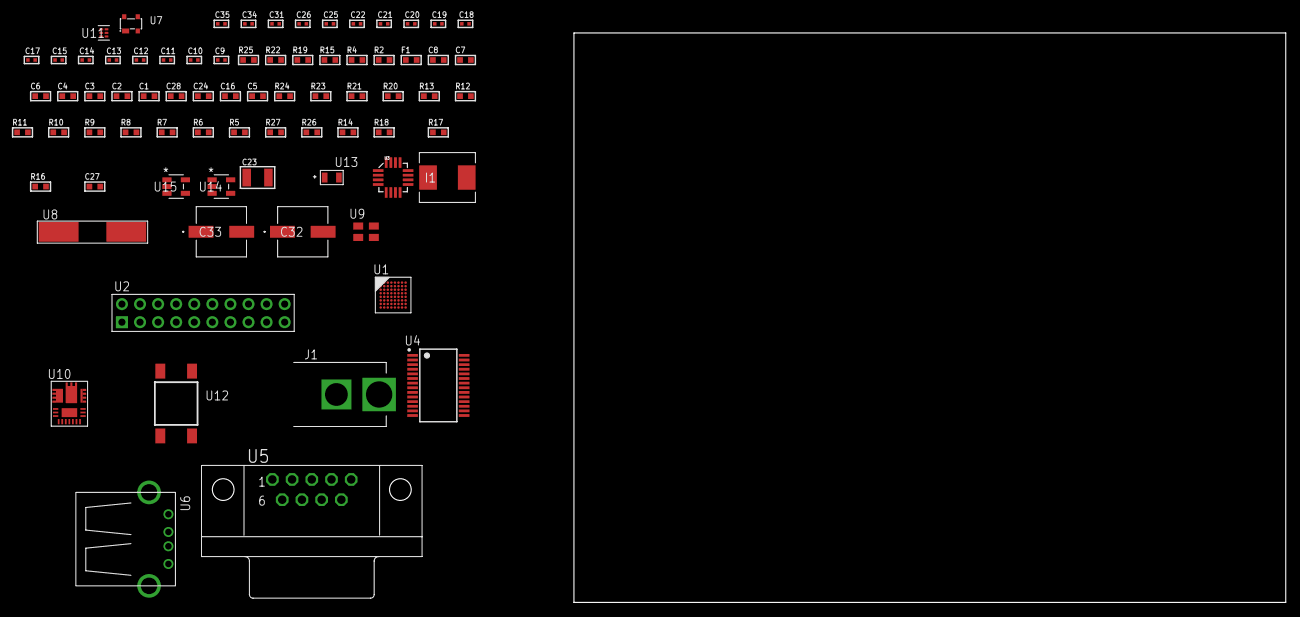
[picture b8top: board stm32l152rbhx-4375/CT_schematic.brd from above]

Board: 2 copper layers, 100.0 x 80.0 mm, 76 parts (0 on the bottom side), 55 nets, no tracks yet.

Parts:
C1, C2, C3, C4, C6: 1e-07; C0603
C5: 4.7e-06; C0603
C7: 1e-08; C0603
C8: 1e-06; C0603
C9, C10: 1e-11; C0402
C11, C12, C17, C18, C19, C20, C21, C25, C26, C31: 1e-07; C0402
C13, C14, C15, C22, C34, C35: 1e-08; C0402
C16: 4.7e-07; C0603
C23: 0.0001; C1210
C24: 2.2e-06; C0603
C27: 7.8444498006919e-09; R0603
C28: 2.7e-07; C0603
C32, C33: 0.0001; EXV-9H
F1: 240.0; L0603
I1: 6.8e-07; IND25X25CZ
J1: PJ-037B; PJ-037B_PACKAGE
R2: 1000.0; R0603
R4: 4700.0; R0603
R5, R6, R7, R8, R9, R10, R11, R12, R13, R23, R24: 10000.0; R0603
R14: 100000.0; R0603
R15: 0.1; R0603
R16: 4030.2416170974; R0603
R17: 719.68600305311; R0603
R18: 64.984347826087; R0603
R19: 130.0; R0603
R20: 39000.0; R0603
R21: 49900.0; R0603
R22: 5600.0; R0603
R25: 9100.0; R0603
R26: 680000.0; R0603
R27: 120000.0; R0603
U1: STM32L152RBH6; TFBGA64
U2: TST-110-05-T-D-RA
U3: l3g4200d; LGA-16
U4: ST3241EBPR; SSOP-28
U5: 182-009-113R531; 182-009-MALE
U6: 61400416021; USB-A-H
U7: prtr5v0u2ax; SOT143B
U8: ABLS-25.000MHZ-B2F-T
U9: ASEK-32.768KHz-ECST; ASEK
U10: IR3899MTR1PBF
U11: TPS3895ADRYR; SON-6
U12: 4-1437565-2; SW_4-1437565-2
U13: Q65110A2395; LGM67K-G1J2-24-Z
U14, U15: nc7sz125m5x; NC7SZ125M5X

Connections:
CLK_CRYSTAL_U1_C1: C9.1, U1.C1, U8.1
CLK_CRYSTAL_U1_D1: C10.1, U1.D1, U8.2
CLK_U1_A1: U1.A1, U9.3
GND: C1.2, C2.2, C3.2, C4.2, C5.2, C6.2, C7.2, C8.2, C9.2, C10.2, C11.2, C12.2, C13.2, C14.2, C15.2, C17.2, C20.2, C21.2, C22.2, C24.2, C25.2, C26.2, C31.2, C32.2, C33.2, C34.2, C35.2, J1.2, R2.2, R5.2, R11.2, R12.1, R12.2, R15.1, R15.2, R17.2, R20.2, R22.2, R25.2, R27.2, U1.C2, U1.D4, U1.D5, U1.D6, U1.F1, U2.4, U2.6, U2.8, U2.10, U2.12, U2.14, U2.16, U2.18, U2.20, U3.8, U3.9, U3.10, U3.11, U3.12, U3.13, U4.23, U4.25, U5.5, U6.4, U6.5, U6.6, U7.1, U9.2, U10.4, U10.11, U10.17, U11.2, U13.C, U14.2, U14.3, U15.1, U15.3
NET_U1_B2: C6.1, U1.B2
NET_U1_B4: R5.1, U1.B4
NET_U1_E1: R4.1, U1.E1, U15.4
NET_U1_H1: C7.1, C8.1, F1.1, U1.G1, U1.H1
NET_U1_H8: U12.3, U12.4
NET_U2_19: R11.1, U2.19
NET_U3_14: C15.1, C16.1, U3.14
NET_U4_1: C19.1, U4.1
NET_U4_2: C19.2, U4.2
NET_U4_3: C21.1, U4.3
NET_U4_22: R14.1, U4.22
NET_U4_24: C18.2, U4.24
NET_U4_27: C20.1, U4.27
NET_U4_28: C18.1, U4.28
NET_U5_2: U4.4, U5.2
NET_U5_3: U4.9, U5.3
NET_U5_7: U4.5, U5.7
NET_U5_8: U4.10, U5.8
NET_U7_4: U6.1, U7.4
NET_U10_1: C27.1, R16.1, R17.1, R18.1, R19.1, U10.1, U10.8
NET_U10_2: C26.1, U10.2
NET_U10_3: C27.2, C28.1, C28.2, U10.3
NET_U10_5: R20.1, U10.5
NET_U10_10: C24.1, U10.10
NET_U10_12: C23.1, I1.1, U10.12
NET_U10_14: C23.2, U10.14
NET_U10_15: R21.1, R22.1, U10.15
NET_U10_ATNET_3: I1.2, R16.2
NET_U10_ATNET_4: C28.2, R18.2
NET_U11_1: R24.1, R25.1, U11.1
NET_U11_3: R26.2, R27.1, U11.3
NET_U11_4: R23.1, U11.4, U14.4, U15.2
NET_U12_1: R2.1, U12.1, U12.2
PROC_SPI1_MISO: U1.G4, U3.4
PROC_SPI1_MOSI: U1.C4, U3.3
PROC_SPI1_NSS: R13.1, U1.H3, U3.5
PROC_SPI1_SCK: U1.F4, U3.2
PROC_SYS_JTCK_SWCLK: R9.1, U1.A7, U2.9
PROC_SYS_JTDI: R7.1, U1.A6, U2.5
PROC_SYS_JTDO_TRACESWO: U1.A5, U2.13
PROC_SYS_JTMS_SWDIO: R8.1, U1.A8, U2.7
PROC_SYS_JTRST: R6.1, U1.A4, U2.3
PROC_USART2_CTS: U1.G2, U4.13
PROC_USART2_RTS: U1.H2, U4.18
PROC_USART2_RX: U1.G3, U4.19
PROC_USART2_TX: U1.F3, U4.14
PROC_USB_DM: U1.C8, U6.2, U7.3
PROC_USB_DP: U1.B8, U6.3, U7.2
RST_OUT_U2_SRESET_B: R10.1, U2.15, U14.1
VCC_S1_16V1: C25.1, C32.1, C33.1, J1.1, R21.2, U10.9
VCC_TIER1_3V3: C1.1, C2.1, C3.1, C4.1, C5.1, C11.1, C12.1, C13.1, C14.1, C17.1, C22.1, C31.1, C34.1, C35.1, F1.2, I1.2, R4.2, R6.2, R7.2, R8.2, R9.2, R10.2, R13.2, R14.2, R16.2, R23.2, R24.2, R26.1, U1.D2, U1.E4, U1.E5, U1.E6, U2.1, U2.2, U3.1, U3.15, U3.16, U4.26, U9.4, U11.6, U14.5, U15.5
